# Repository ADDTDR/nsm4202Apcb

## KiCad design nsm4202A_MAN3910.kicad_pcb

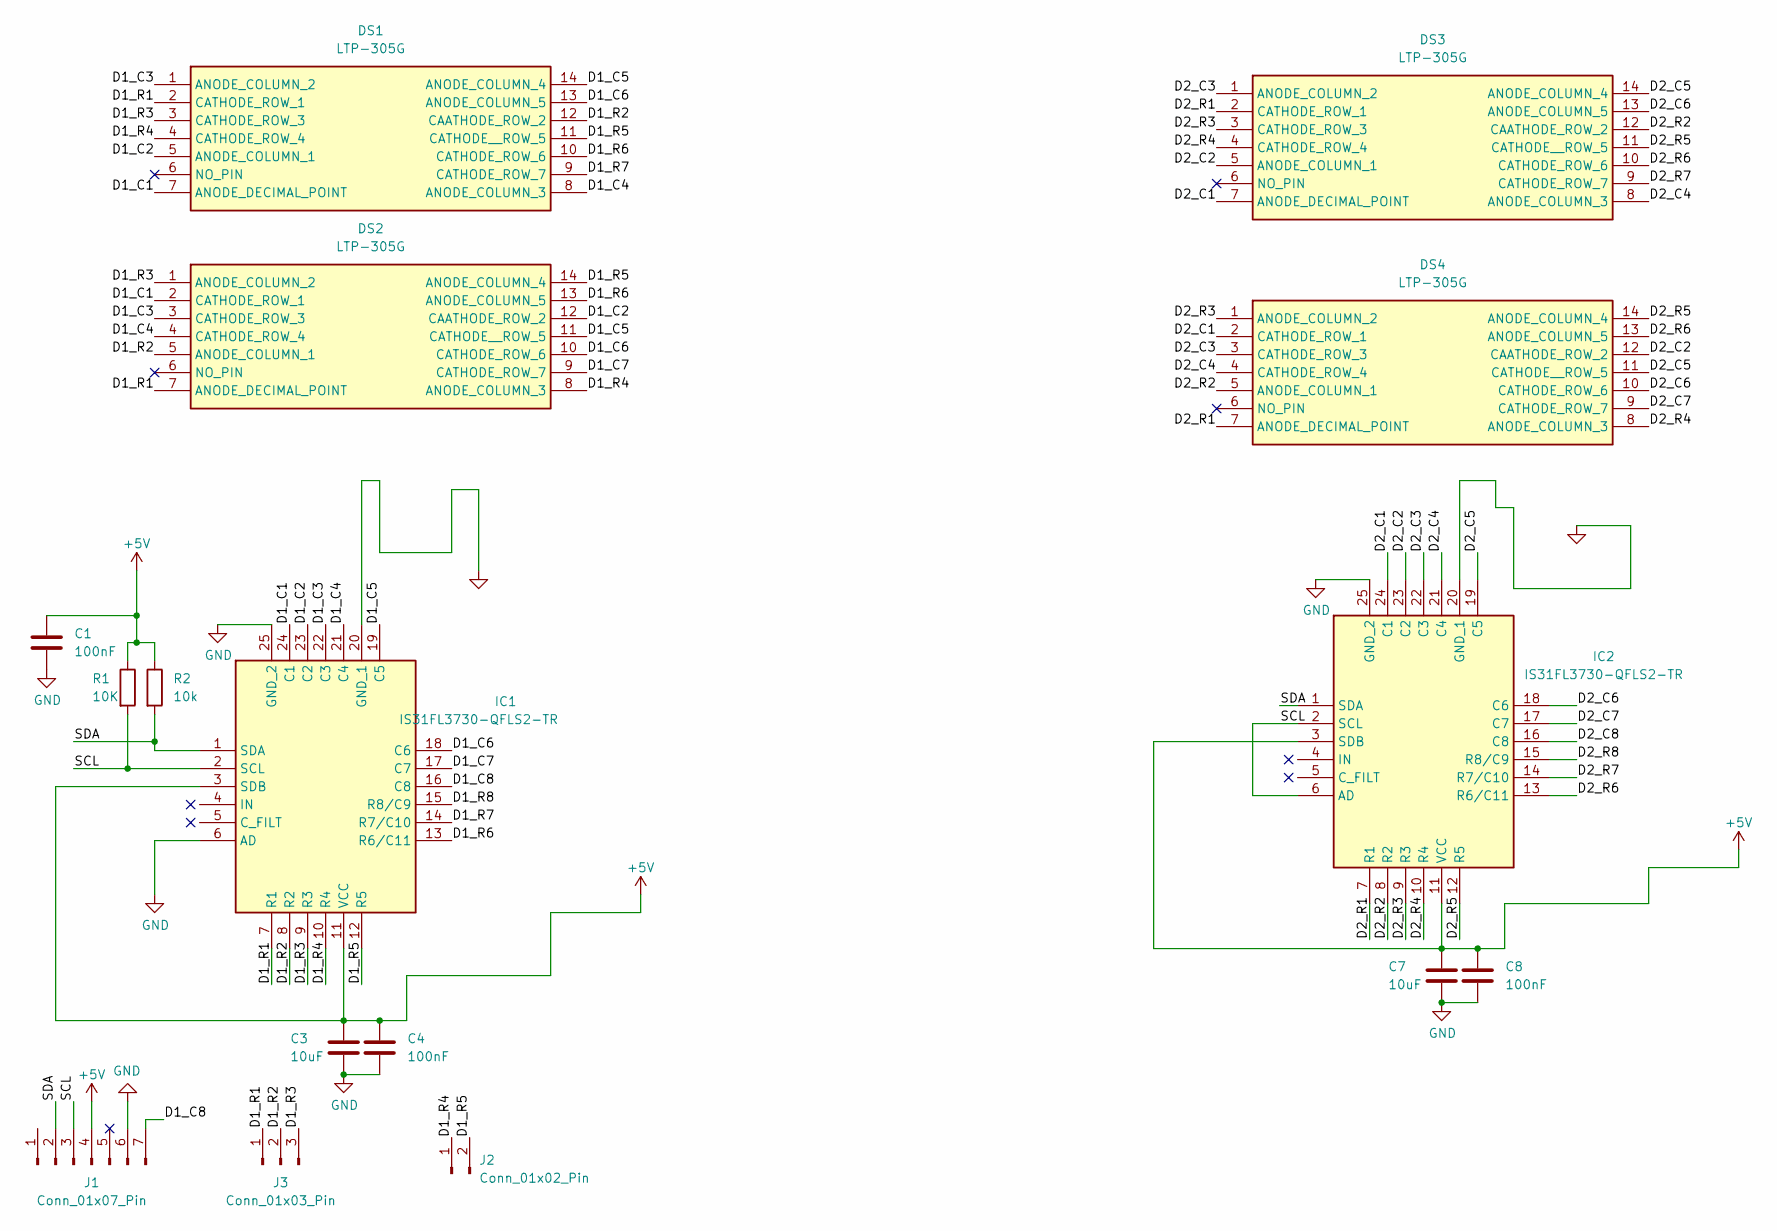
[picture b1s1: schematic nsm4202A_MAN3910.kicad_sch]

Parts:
C1, C4, C8: 100nF; C_0603_1608Metric_Pad1.08x0.95mm_HandSolder
C3, C7: 10uF; C_0805_2012Metric
DS1, DS2, DS3, DS4: LTP-305G; DIPS762W50P254L1850H400Q14N; Manufacturer_Part_Number LTP-305G; Mouser Part Number 859-LTP-305G
IC1, IC2: IS31FL3730-QFLS2-TR; QFN50P400X400X80-25N-D; Manufacturer_Part_Number IS31FL3730-QFLS2-TR; Mouser Part Number 870-IS31FL3730QFLS2R
J1: Conn_01x07_Pin; PinHeader_1x07_P2.54mm_Vertical
J2: Conn_01x02_Pin; PinHeader_1x02_P2.54mm_Vertical
J3: Conn_01x03_Pin; PinHeader_1x03_P2.54mm_Vertical
R1: 10K; R_0603_1608Metric_Pad0.98x0.95mm_HandSolder
R2: 10k; R_0603_1608Metric_Pad0.98x0.95mm_HandSolder

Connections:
+5V: C1.1, C3.1, C4.1, C7.1, C8.1, IC1.3 (SDB), IC1.11 (VCC), IC2.3 (SDB), IC2.11 (VCC), J1.4, R1.1, R2.1
/D1_C1: DS1.7 (ANODE_DECIMAL_POINT), DS2.2 (CATHODE_ROW_1), IC1.24 (C1)
/D1_C2: DS1.5 (ANODE_COLUMN_1), DS2.12 (CAATHODE_ROW_2), IC1.23 (C2)
/D1_C3: DS1.1 (ANODE_COLUMN_2), DS2.3 (CATHODE_ROW_3), IC1.22 (C3)
/D1_C4: DS1.8 (ANODE_COLUMN_3), DS2.4 (CATHODE_ROW_4), IC1.21 (C4)
/D1_C5: DS1.14 (ANODE_COLUMN_4), DS2.11 (CATHODE__ROW_5), IC1.19 (C5)
/D1_C6: DS1.13 (ANODE_COLUMN_5), DS2.10 (CATHODE_ROW_6), IC1.18 (C6)
/D1_C7: DS2.9 (CATHODE_ROW_7), IC1.17 (C7)
/D1_C8: IC1.16 (C8), J1.7
/D1_R1: DS1.2 (CATHODE_ROW_1), DS2.7 (ANODE_DECIMAL_POINT), IC1.7 (R1), J3.1
/D1_R2: DS1.12 (CAATHODE_ROW_2), DS2.5 (ANODE_COLUMN_1), IC1.8 (R2), J3.2
/D1_R3: DS1.3 (CATHODE_ROW_3), DS2.1 (ANODE_COLUMN_2), IC1.9 (R3), J3.3
/D1_R4: DS1.4 (CATHODE_ROW_4), DS2.8 (ANODE_COLUMN_3), IC1.10 (R4), J2.1
/D1_R5: DS1.11 (CATHODE__ROW_5), DS2.14 (ANODE_COLUMN_4), IC1.12 (R5), J2.2
/D1_R6: DS1.10 (CATHODE_ROW_6), DS2.13 (ANODE_COLUMN_5), IC1.13 (R6/C11)
/D1_R7: DS1.9 (CATHODE_ROW_7), IC1.14 (R7/C10)
/D1_R8: IC1.15 (R8/C9)
/D2_C1: DS3.7 (ANODE_DECIMAL_POINT), DS4.2 (CATHODE_ROW_1), IC2.24 (C1)
/D2_C2: DS3.5 (ANODE_COLUMN_1), DS4.12 (CAATHODE_ROW_2), IC2.23 (C2)
/D2_C3: DS3.1 (ANODE_COLUMN_2), DS4.3 (CATHODE_ROW_3), IC2.22 (C3)
/D2_C4: DS3.8 (ANODE_COLUMN_3), DS4.4 (CATHODE_ROW_4), IC2.21 (C4)
/D2_C5: DS3.14 (ANODE_COLUMN_4), DS4.11 (CATHODE__ROW_5), IC2.19 (C5)
/D2_C6: DS3.13 (ANODE_COLUMN_5), DS4.10 (CATHODE_ROW_6), IC2.18 (C6)
/D2_C7: DS4.9 (CATHODE_ROW_7), IC2.17 (C7)
/D2_C8: IC2.16 (C8)
/D2_R1: DS3.2 (CATHODE_ROW_1), DS4.7 (ANODE_DECIMAL_POINT), IC2.7 (R1)
/D2_R2: DS3.12 (CAATHODE_ROW_2), DS4.5 (ANODE_COLUMN_1), IC2.8 (R2)
/D2_R3: DS3.3 (CATHODE_ROW_3), DS4.1 (ANODE_COLUMN_2), IC2.9 (R3)
/D2_R4: DS3.4 (CATHODE_ROW_4), DS4.8 (ANODE_COLUMN_3), IC2.10 (R4)
/D2_R5: DS3.11 (CATHODE__ROW_5), DS4.14 (ANODE_COLUMN_4), IC2.12 (R5)
/D2_R6: DS3.10 (CATHODE_ROW_6), DS4.13 (ANODE_COLUMN_5), IC2.13 (R6/C11)
/D2_R7: DS3.9 (CATHODE_ROW_7), IC2.14 (R7/C10)
/D2_R8: IC2.15 (R8/C9)
/SCL: IC1.2 (SCL), IC2.2 (SCL), IC2.6 (AD), J1.3, R1.2
/SDA: IC1.1 (SDA), IC2.1 (SDA), J1.2, R2.2
GND: C1.2, C3.2, C4.2, C7.2, C8.2, IC1.6 (AD), IC1.20 (GND_1), IC1.25 (GND_2), IC2.20 (GND_1), IC2.25 (GND_2), J1.6

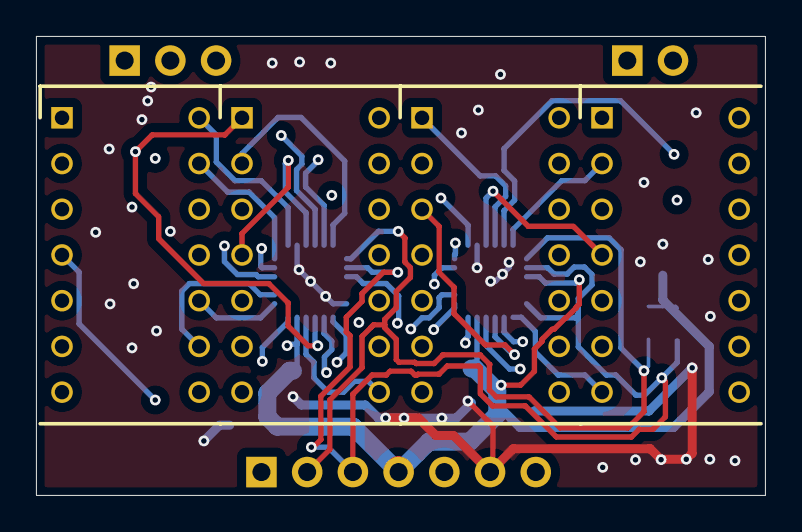
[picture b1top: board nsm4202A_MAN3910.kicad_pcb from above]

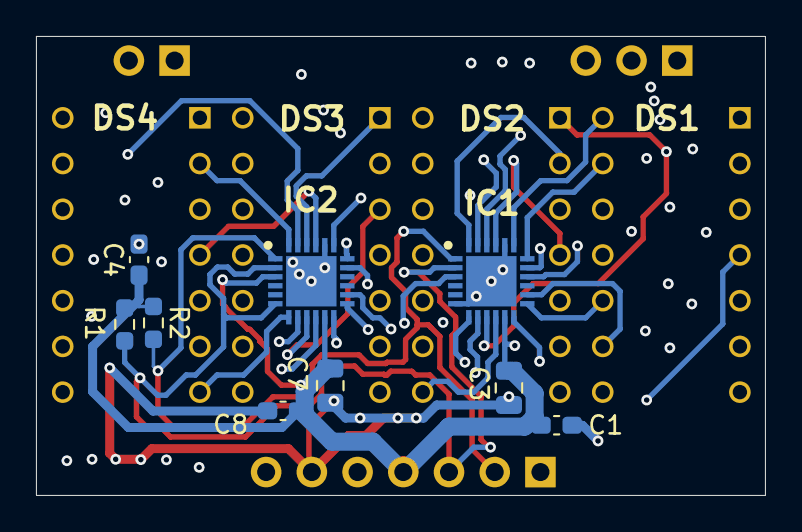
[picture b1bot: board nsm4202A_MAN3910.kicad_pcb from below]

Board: 4 copper layers, 40.5 x 25.5 mm, 16 parts (12 on the bottom side), 33 nets.

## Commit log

2025-12-10 Move connectors
2025-12-10 Start trace
2025-12-12 Add models
